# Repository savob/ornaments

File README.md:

# Ornaments

Simple circuit board tree ornaments to distribute to friends and family.

## Software Used

2019's ornaments were originally designed in EAGLE and then imported to KiCad 7.0.10.

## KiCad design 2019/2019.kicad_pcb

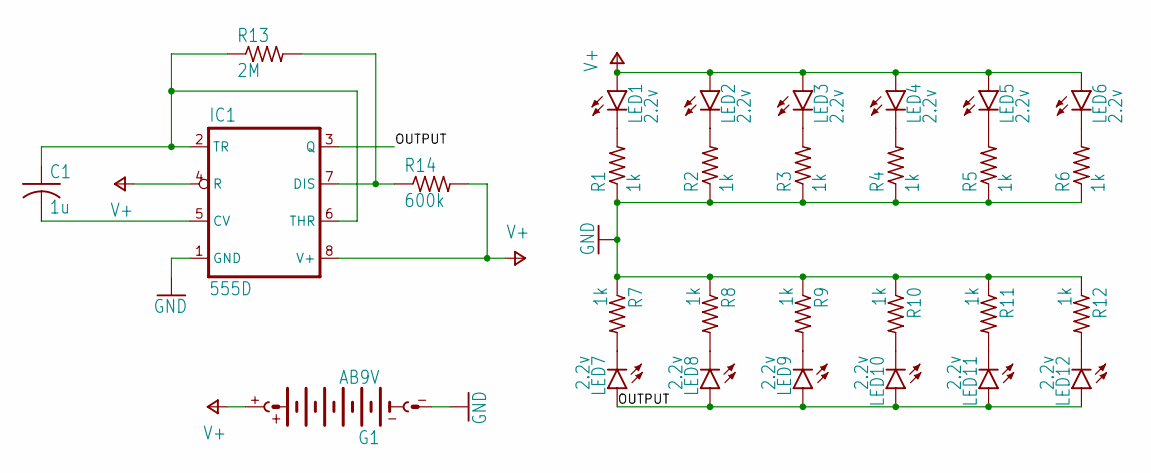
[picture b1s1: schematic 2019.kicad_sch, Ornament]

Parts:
C1: 1u; C0603
G1: AB9V
IC1: 555D; SO08
LED1, LED2, LED3, LED4, LED5, LED6, LED7, LED8, LED9, LED10, LED11, LED12: 2.2v; LED5MM
R1, R2, R3, R4, R5, R6, R7, R8, R9, R10, R11, R12: 1k; R0603
R13: 2M; R0603
R14: 600k; R0603

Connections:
GND: G1.-, IC1.1 (GND), R1.1, R2.1, R3.1, R4.1, R5.1, R6.1, R7.1, R8.1, R9.1, R10.1, R11.1, R12.1
unnamed: LED1.K (C), R1.2
unnamed: IC1.7 (DIS), R13.2, R14.1
unnamed: LED2.K (C), R2.2
unnamed: C1.2, IC1.5 (CV)
unnamed: C1.1, IC1.2 (TR), IC1.6 (THR), R13.1
unnamed: LED3.K (C), R3.2
unnamed: LED4.K (C), R4.2
unnamed: LED5.K (C), R5.2
unnamed: LED6.K (C), R6.2
unnamed: LED12.K (C), R12.2
unnamed: LED11.K (C), R11.2
unnamed: LED10.K (C), R10.2
unnamed: LED9.K (C), R9.2
unnamed: LED8.K (C), R8.2
unnamed: LED7.K (C), R7.2
OUTPUT: IC1.3 (Q), LED7.A, LED8.A, LED9.A, LED10.A, LED11.A, LED12.A
V+: G1.+, IC1.4 (R), IC1.8 (V+), LED1.A, LED2.A, LED3.A, LED4.A, LED5.A, LED6.A, R14.2

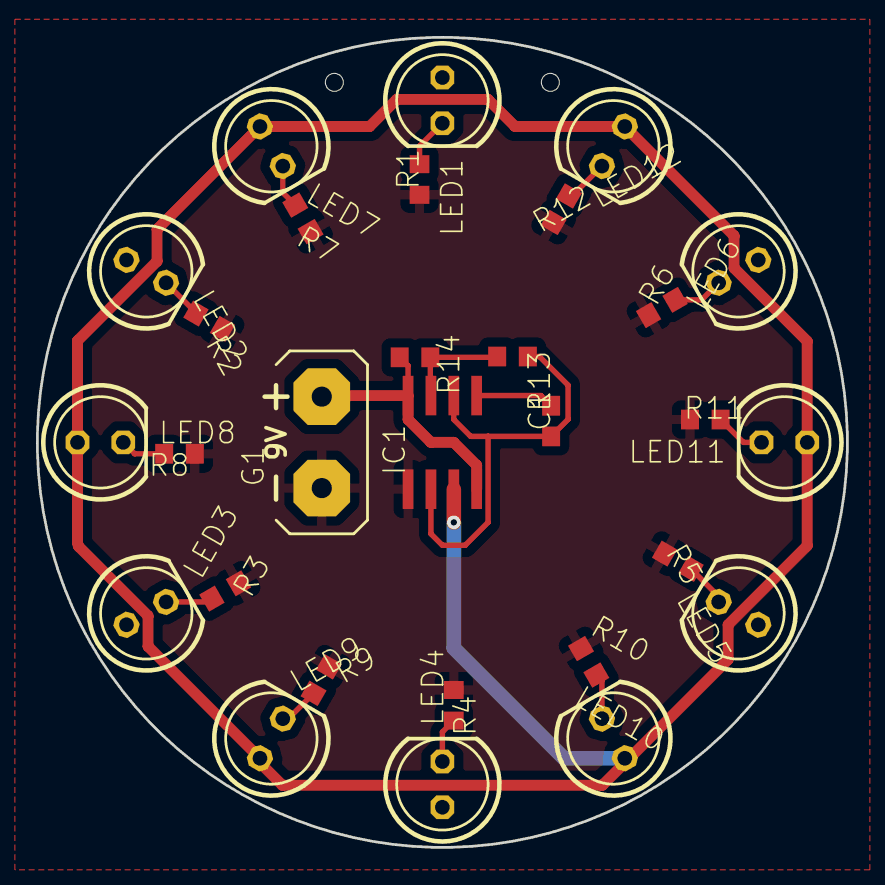
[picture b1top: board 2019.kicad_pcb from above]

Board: 2 copper layers, 45.0 x 45.0 mm, 31 parts (0 on the bottom side), 18 nets.

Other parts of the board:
@HOLE0, @HOLE1: (no value)

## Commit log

2024-01-04 Upload of 2019 ornament
2024-01-04 Added licence
